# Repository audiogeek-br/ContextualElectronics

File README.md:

ContextualElectronics
=====================

Contextual Electronics Course Work

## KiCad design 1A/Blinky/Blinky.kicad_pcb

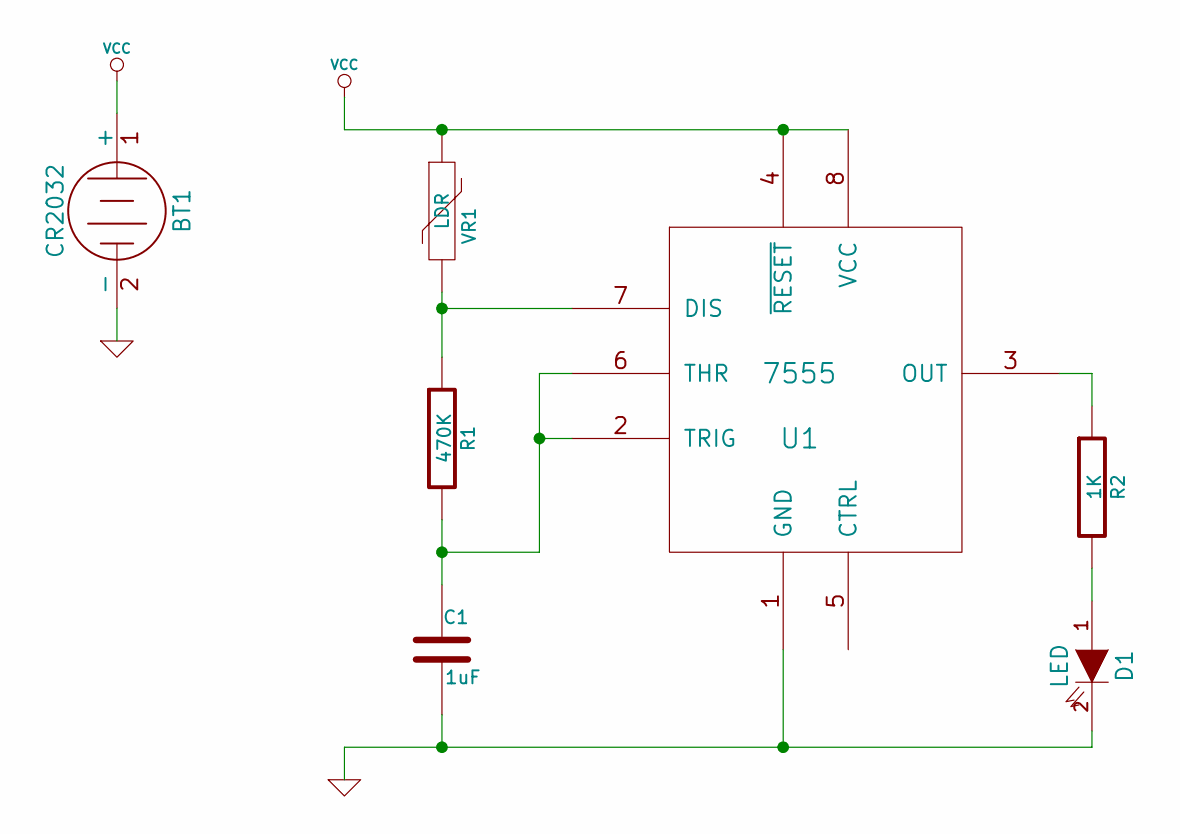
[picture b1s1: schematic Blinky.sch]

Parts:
BT1: CR2032
C1: 1uF
D1: LED
R1: 470K
R2: 1K
U1: 7555
VR1: LDR

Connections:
GND: BT1.2 (-), C1.2, D1.2 (K), U1.1 (GND)
unnamed: R2.1, U1.3 (OUT)
unnamed: D1.1 (A), R2.2
unnamed: C1.1, R1.2, U1.2 (TRIG), U1.6 (THR)
unnamed: R1.1, U1.7 (DIS), VR1.2
VCC: BT1.1 (+), U1.4 (~RESET), U1.8 (VCC), VR1.1

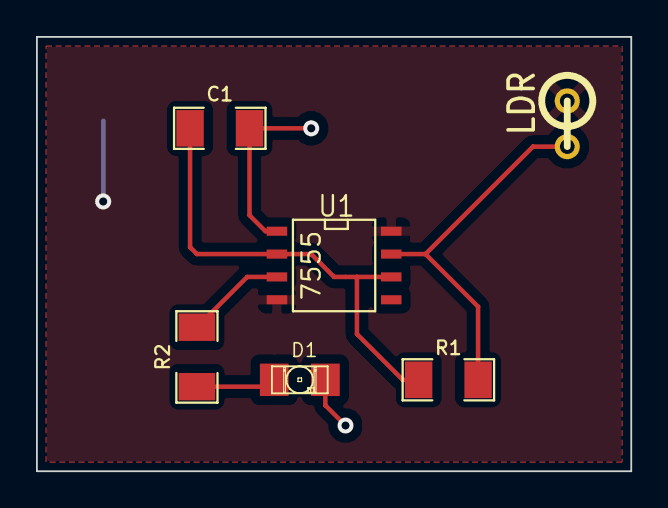
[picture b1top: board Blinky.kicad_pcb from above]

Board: 2 copper layers, 33.0 x 24.1 mm, 7 parts (1 on the bottom side), 6 nets.

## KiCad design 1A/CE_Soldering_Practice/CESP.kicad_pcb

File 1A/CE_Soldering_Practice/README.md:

Soldering Practice Board
========================

Please see the Docs/ directory for a bill of materials with digikey and
element14 part numbers, plus an oshpark rendering of the front and back of the
board.

Thanks!

Sam

I couldn't bring myself to just drop components on a board and have them not
do anything, so this board will (hopefully!) blink 8 LEDs in two alternating
groups of four.

The circuit is pretty convoluted, just to increase the part count and the
number of different footprints used:

* 0603 (8 components)
* 0805 (15 components)
* 1206 (8 components))
* SOT23 (4 components)
* SOIC8 (1 component)
* TSSOP14 (1 component)
* MSOP (2 components)
* Through-hole (3 components)

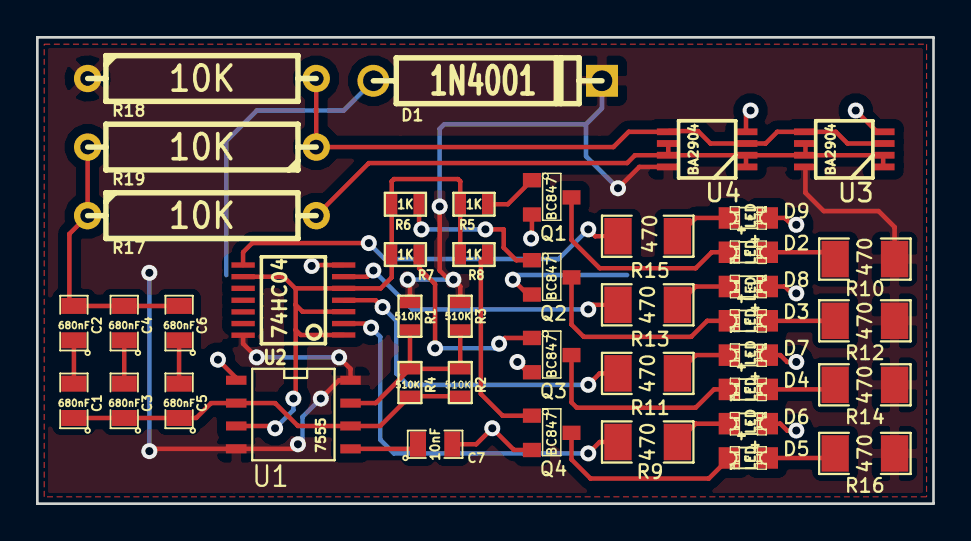
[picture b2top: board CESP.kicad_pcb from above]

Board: 2 copper layers, 49.8 x 25.9 mm, 44 parts (1 on the bottom side), 32 nets.

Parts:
BT1: BATTERY; BU2032SM-BT-GTR
C1, C2, C3, C4, C5, C6: 680nF; SM0805
C7: 10nF; SM0805
D1: 1N4001; D5
D2, D3, D4, D5, D6, D7, D8, D9: LED; LED-0805
Q1, Q2, Q3, Q4: BC847; SOT23
R1, R2, R3, R4: 510K; SM0603
R5, R6, R7, R8: 1K; SM0603
R9, R10, R11, R12, R13, R14, R15, R16: 470; SM1206
R17, R18, R19: 10K; R5
U1: 7555; SO8N
U2: 74HC04; TSSOP14
U3, U4: BA2904; MSOP_8

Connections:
GND: BT1.2, C2.2, C4.2, C6.2, C7.2, D6.2, D7.2, D8.2, D9.2, Q1.2, Q2.2, Q3.2, Q4.2, R17.1, R19.2, U1.1, U2.7, U3.4, U4.4
unnamed: R18.2, R19.1, U3.3, U3.5, U4.3, U4.5
unnamed: R5.1, R6.1, R7.1, R8.1, U1.3, U2.1, U2.3, U2.5, U2.9
unnamed: Q1.1, R5.2
unnamed: Q2.1, R6.2
unnamed: BT1.1, D1.1
unnamed: R17.2, U3.1, U3.2, U3.6, U3.7, U4.1, U4.2, U4.6, U4.7
unnamed: Q3.1, R7.2
unnamed: Q4.1, R8.2
unnamed: R9.1, U2.2
unnamed: C7.1, U1.5
unnamed: C1.1, C3.1, C5.1, R2.2, R4.2, U1.2, U1.6
unnamed: D6.1, R9.2
unnamed: D2.1, R10.1
unnamed: D2.2, Q1.3
unnamed: R11.1, U2.4
unnamed: D7.1, R11.2
unnamed: D3.1, R12.1
unnamed: R13.1, U2.6
unnamed: D8.1, R13.2
unnamed: D4.1, R14.1
unnamed: R15.1, U2.8
unnamed: D9.1, R15.2
unnamed: D5.1, R16.1
unnamed: D3.2, Q2.3
unnamed: D4.2, Q3.3
unnamed: D5.2, Q4.3
unnamed: C1.2, C2.1
unnamed: C3.2, C4.1
unnamed: C5.2, C6.1
unnamed: R1.2, R2.1, R3.2, R4.1, U1.7
VCC: D1.2, R1.1, R3.1, R10.2, R12.2, R14.2, R16.2, R18.1, U1.4, U1.8, U2.14, U3.8, U4.8

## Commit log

2014-01-27 Add template soldering practice project
2014-01-27 Add Blinky
2014-01-27 Add Blinky screenshot for good measure
2014-01-27 My soldering practice board design
2014-01-30 Arduino board silhouette
2014-01-31 Remove references to unnecessary libraries; export PCB as old .brd format
2014-01-31 Revert "Remove references to unnecessary libraries; export PCB as old .brd format"
    This reverts commit 42e6709df17a427ff7cc4c819a4122dc338fac0c.
2014-01-31 Remove references to unnecessary libraries
2014-01-31 Add missing VCC trace
2014-01-31 Export PCB as old-version .brd file
2014-01-31 Regenerate gerber files
2014-01-31 Add .gitattributes and .gitignore from CE's BenchBudEE template
2014-01-31 Create empty BenchBudEE project
2014-01-31 Create BenchBudEE component sheets from block diagram
2014-01-31 Prevent commit warnings about line endings (hopefully)
2014-01-31 Define component inputs and outputs
2014-02-01 Add readme file
